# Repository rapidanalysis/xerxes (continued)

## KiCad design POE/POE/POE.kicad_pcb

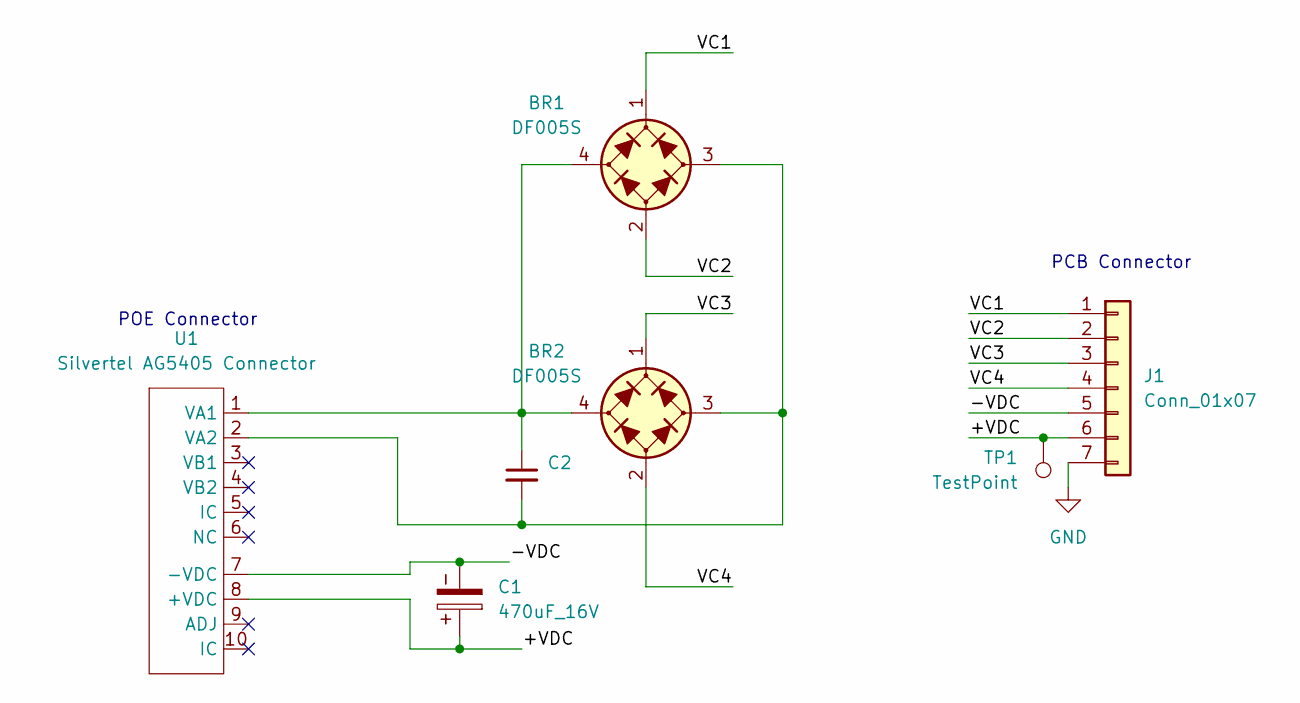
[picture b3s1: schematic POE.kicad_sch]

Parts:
BR1, BR2: DF005S; Diode_Bridge_Vishay_DFS
C1: 470uF_16V; CP_Radial_D8.0mm_P3.50mm
C2: 10nF; C_0402_1005Metric; Part Number 10 nf Capacitor 0402
J1: Conn_01x07; PinHeader_1x07_P2.54mm_Vertical
TP1: TestPoint; TestPoint_Pad_2.0x2.0mm
U1: Silvertel AG5405 Connector; AG5405

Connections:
/+VDC: C1.1, J1.6, TP1.1, U1.8 (+VDC)
/-VDC: C1.2, J1.5, U1.7 (-VDC)
/VC1: BR1.1 (+), J1.1
/VC2: BR1.2 (-), J1.2
/VC3: BR2.1 (+), J1.3
/VC4: BR2.2 (-), J1.4
GND: J1.7
unnamed: BR1.3 (1), BR2.3 (1), C2.2, U1.2 (VA2)
unnamed: BR1.4 (2), BR2.4 (2), C2.1, U1.1 (VA1)

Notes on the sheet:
POE Connector
PCB Connector

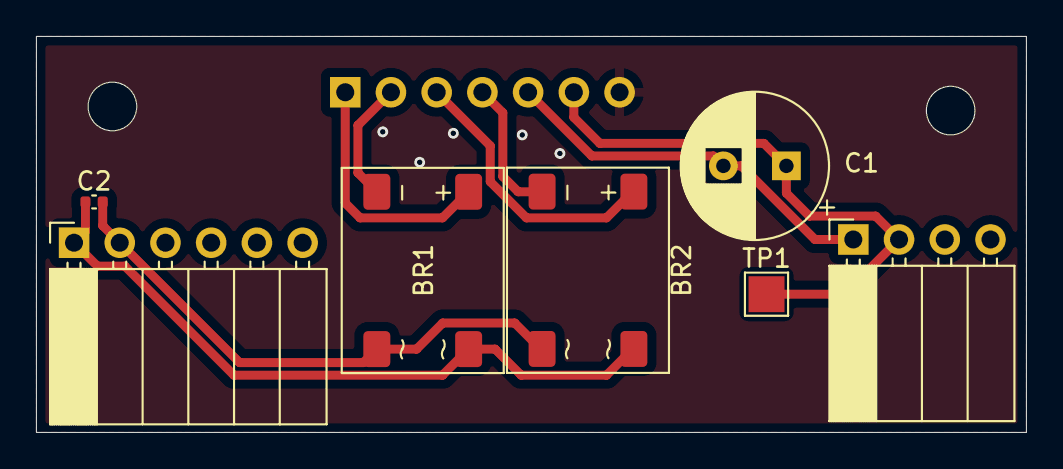
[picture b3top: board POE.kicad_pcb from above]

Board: 2 copper layers, 55.0 x 22.0 mm, 7 parts (1 on the bottom side), 8 nets.

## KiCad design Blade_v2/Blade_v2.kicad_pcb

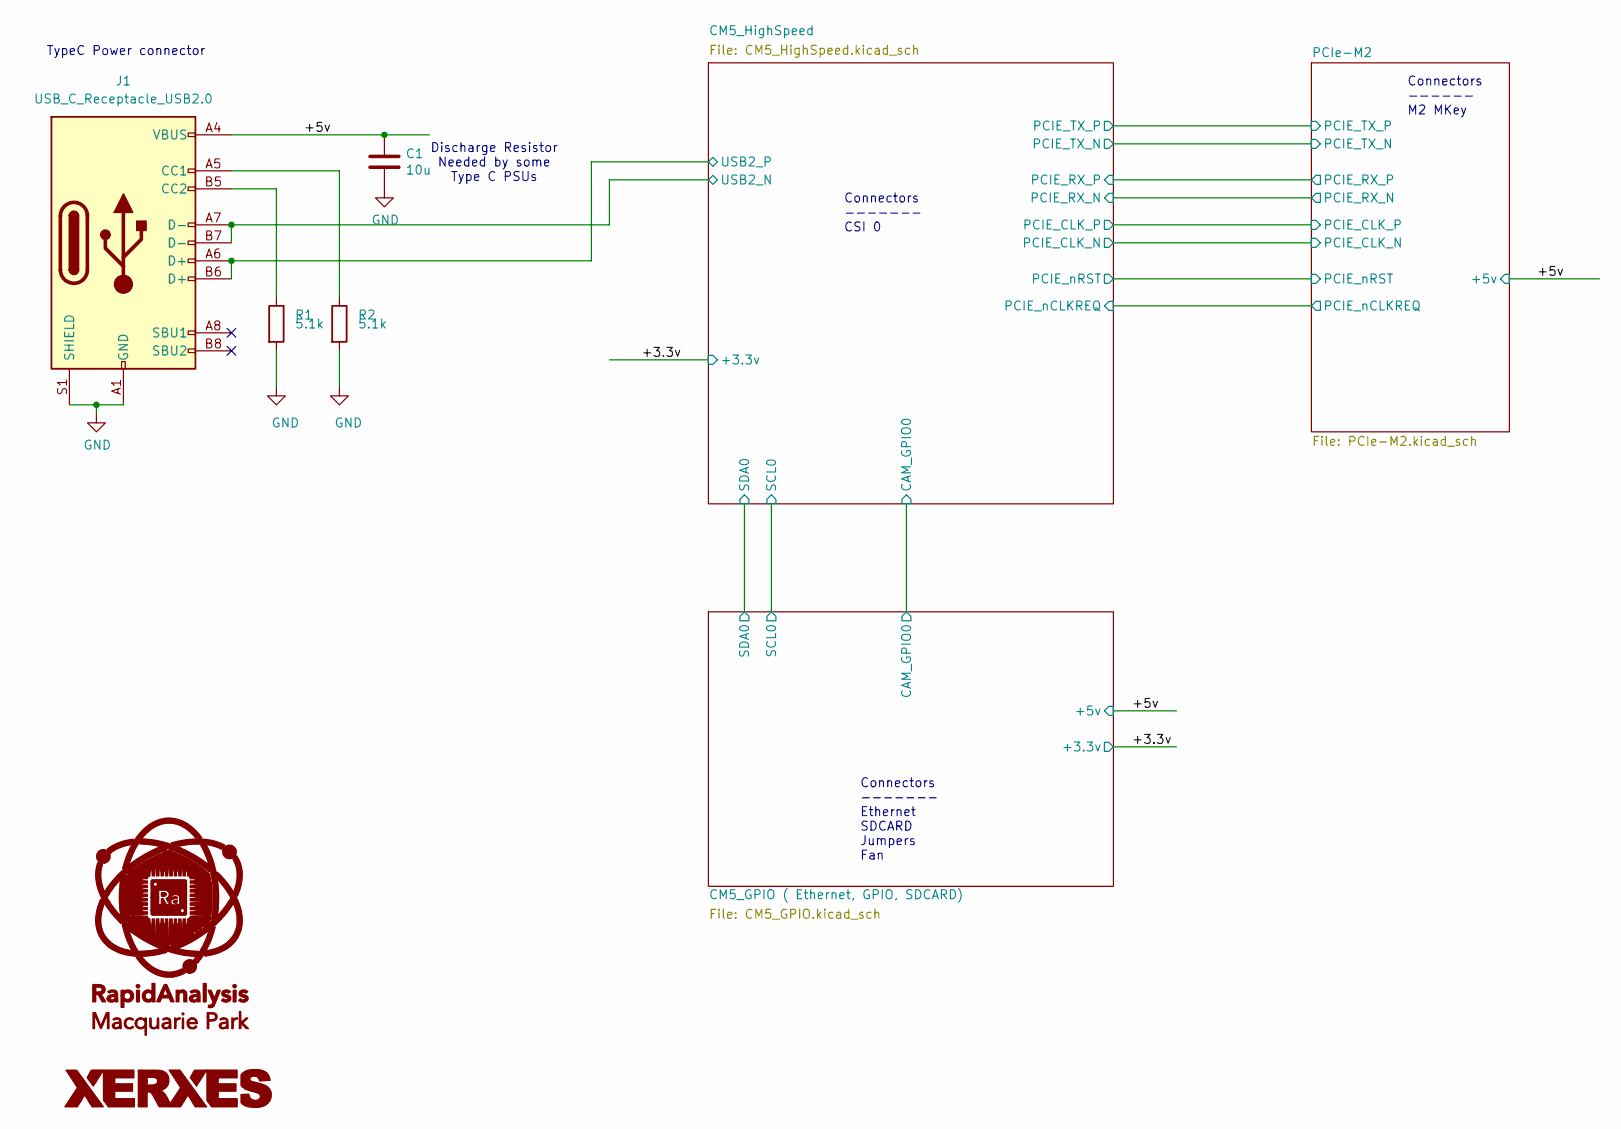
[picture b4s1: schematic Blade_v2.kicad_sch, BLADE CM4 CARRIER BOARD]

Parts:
C1: 10u; C_0402_1005Metric; Part Description 0.1uF 10% 16V Ceramic Capacitor X7R 040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
J1: USB_C_Receptacle_USB2.0; USB_C_Receptacle_GCT_USB4105-xx-A_16P_TopMnt_Horizontal; Part Description USBC USB2 data and power connector
R1, R2: 5.1k; R_0603_1608Metric_Pad0.98x0.95mm_HandSolder; MPN RC0603FR-075K1L; Digi-Key_PN 311-5.10KHRCT-ND

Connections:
/+5v: C1.1, J1.A4 (VBUS), J1.A9 (VBUS), J1.B4 (VBUS), J1.B9 (VBUS); also elsewhere on the board
/CM5_HighSpeed/USB2_N: J1.A7 (D-), J1.B7 (D-); also elsewhere on the board
/CM5_HighSpeed/USB2_P: J1.A6 (D+), J1.B6 (D+); also elsewhere on the board
GND: C1.2, J1.A1 (GND), J1.A12 (GND), J1.B1 (GND), J1.B12 (GND), J1.S1 (SHIELD), R1.2, R2.2; also elsewhere on the board
unnamed: J1.A5 (CC1), R2.1
unnamed: J1.B5 (CC2), R1.1

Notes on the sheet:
Connectors ------ M2 MKey
Connectors ------- Ethernet SDCARD Jumpers Fan
Discharge Resistor Needed by some Type C PSUs
Connectors ------- CSI 0
TypeC Power connector

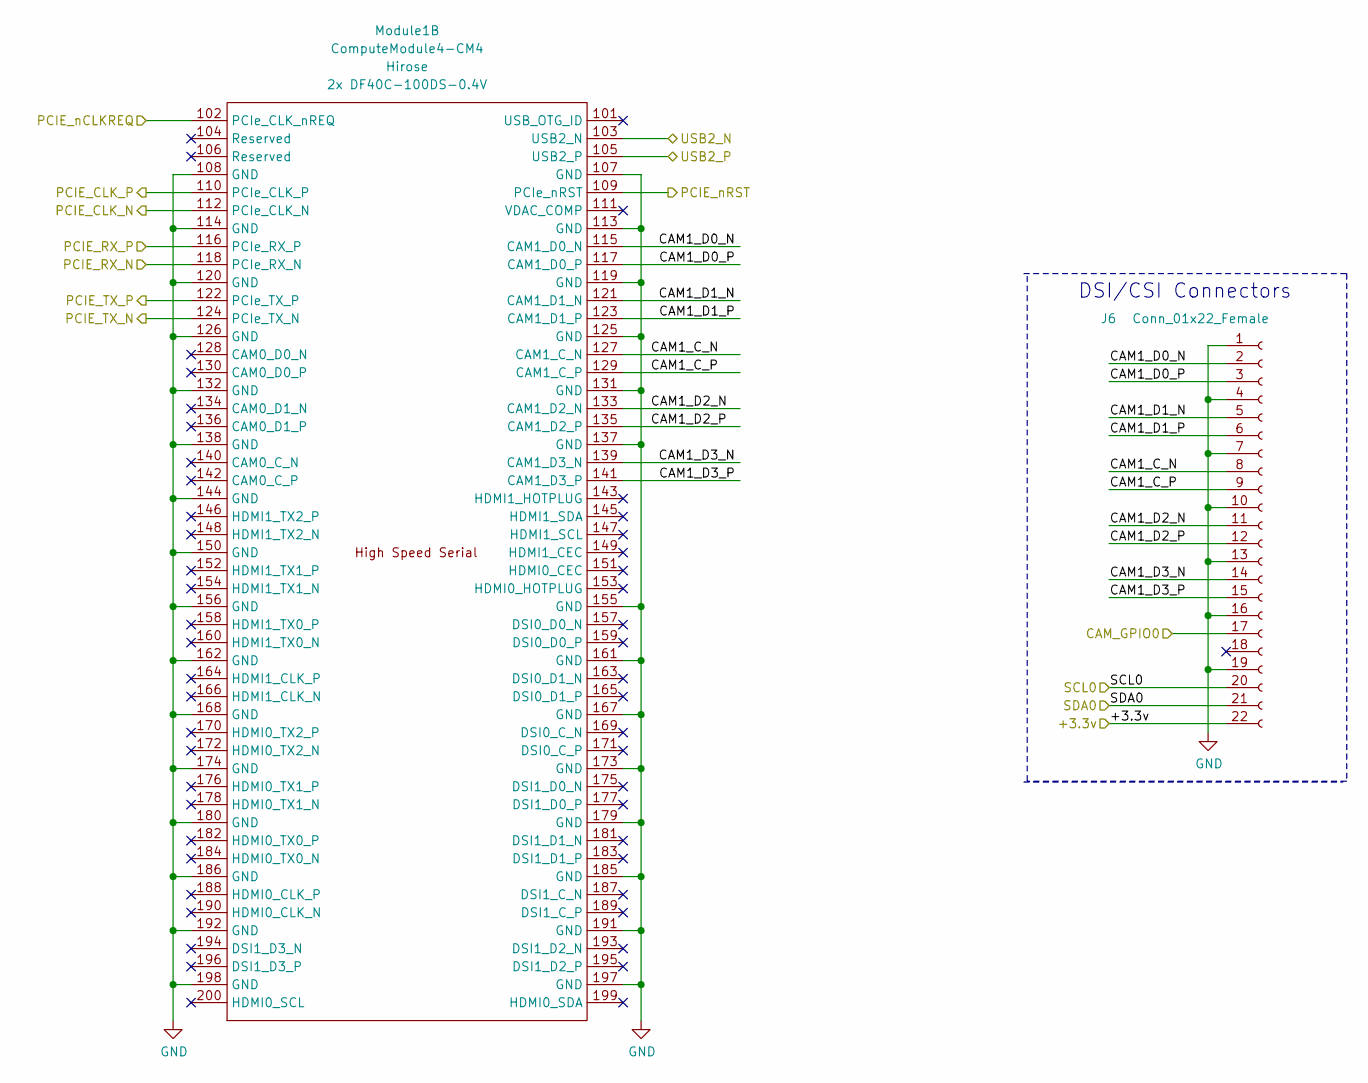
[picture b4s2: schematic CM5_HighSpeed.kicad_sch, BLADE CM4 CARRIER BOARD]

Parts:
J6: Conn_01x22_Female; Hirose_FH12-22S-0.5SH_1x22-1MP_P0.50mm_Horizontal; Part Description 22 Position FFC, FPC Connector Contacts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
Module1: ComputeModule4-CM4; Raspberry-Pi-4-Compute-Module

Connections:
/+3.3v: J6.22; also elsewhere on the board
/CM5_GPIO ( Ethernet, GPIO, SDCARD)/CAM_GPIO0: J6.17; also elsewhere on the board
/CM5_GPIO ( Ethernet, GPIO, SDCARD)/SCL0: J6.20; also elsewhere on the board
/CM5_GPIO ( Ethernet, GPIO, SDCARD)/SDA0: J6.21; also elsewhere on the board
/CM5_HighSpeed/CAM1_C_N: J6.8, Module1.127 (CAM1_C_N)
/CM5_HighSpeed/CAM1_C_P: J6.9, Module1.129 (CAM1_C_P)
/CM5_HighSpeed/CAM1_D0_N: J6.2, Module1.115 (CAM1_D0_N)
/CM5_HighSpeed/CAM1_D0_P: J6.3, Module1.117 (CAM1_D0_P)
/CM5_HighSpeed/CAM1_D1_N: J6.5, Module1.121 (CAM1_D1_N)
/CM5_HighSpeed/CAM1_D1_P: J6.6, Module1.123 (CAM1_D1_P)
/CM5_HighSpeed/CAM1_D2_N: J6.11, Module1.133 (CAM1_D2_N)
/CM5_HighSpeed/CAM1_D2_P: J6.12, Module1.135 (CAM1_D2_P)
/CM5_HighSpeed/CAM1_D3_N: J6.14, Module1.139 (CAM1_D3_N)
/CM5_HighSpeed/CAM1_D3_P: J6.15, Module1.141 (CAM1_D3_P)
/CM5_HighSpeed/PCIE_CLK_N: Module1.112 (PCIe_CLK_N); also elsewhere on the board
/CM5_HighSpeed/PCIE_CLK_P: Module1.110 (PCIe_CLK_P); also elsewhere on the board
/CM5_HighSpeed/PCIE_RX_N: Module1.118 (PCIe_RX_N); also elsewhere on the board
/CM5_HighSpeed/PCIE_RX_P: Module1.116 (PCIe_RX_P); also elsewhere on the board
/CM5_HighSpeed/PCIE_TX_N: Module1.124 (PCIe_TX_N); also elsewhere on the board
/CM5_HighSpeed/PCIE_TX_P: Module1.122 (PCIe_TX_P); also elsewhere on the board
/CM5_HighSpeed/PCIE_nCLKREQ: Module1.102 (PCIe_CLK_nREQ); also elsewhere on the board
/CM5_HighSpeed/PCIE_nRST: Module1.109 (PCIe_nRST); also elsewhere on the board
/CM5_HighSpeed/USB2_N: Module1.103 (USB2_N); also elsewhere on the board
/CM5_HighSpeed/USB2_P: Module1.105 (USB2_P); also elsewhere on the board
GND: J6.1, J6.4, J6.7, J6.10, J6.13, J6.16, J6.19, Module1.107 (GND), Module1.108 (GND), Module1.113 (GND), Module1.114 (GND), Module1.119 (GND), Module1.120 (GND), Module1.125 (GND), Module1.126 (GND), Module1.131 (GND), Module1.132 (GND), Module1.137 (GND), Module1.138 (GND), Module1.144 (GND), Module1.150 (GND), Module1.155 (GND), Module1.156 (GND), Module1.161 (GND), Module1.162 (GND), Module1.167 (GND), Module1.168 (GND), Module1.173 (GND), Module1.174 (GND), Module1.179 (GND), Module1.180 (GND), Module1.185 (GND), Module1.186 (GND), Module1.191 (GND), Module1.192 (GND), Module1.197 (GND), Module1.198 (GND); also elsewhere on the board

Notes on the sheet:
DSI/CSI Connectors

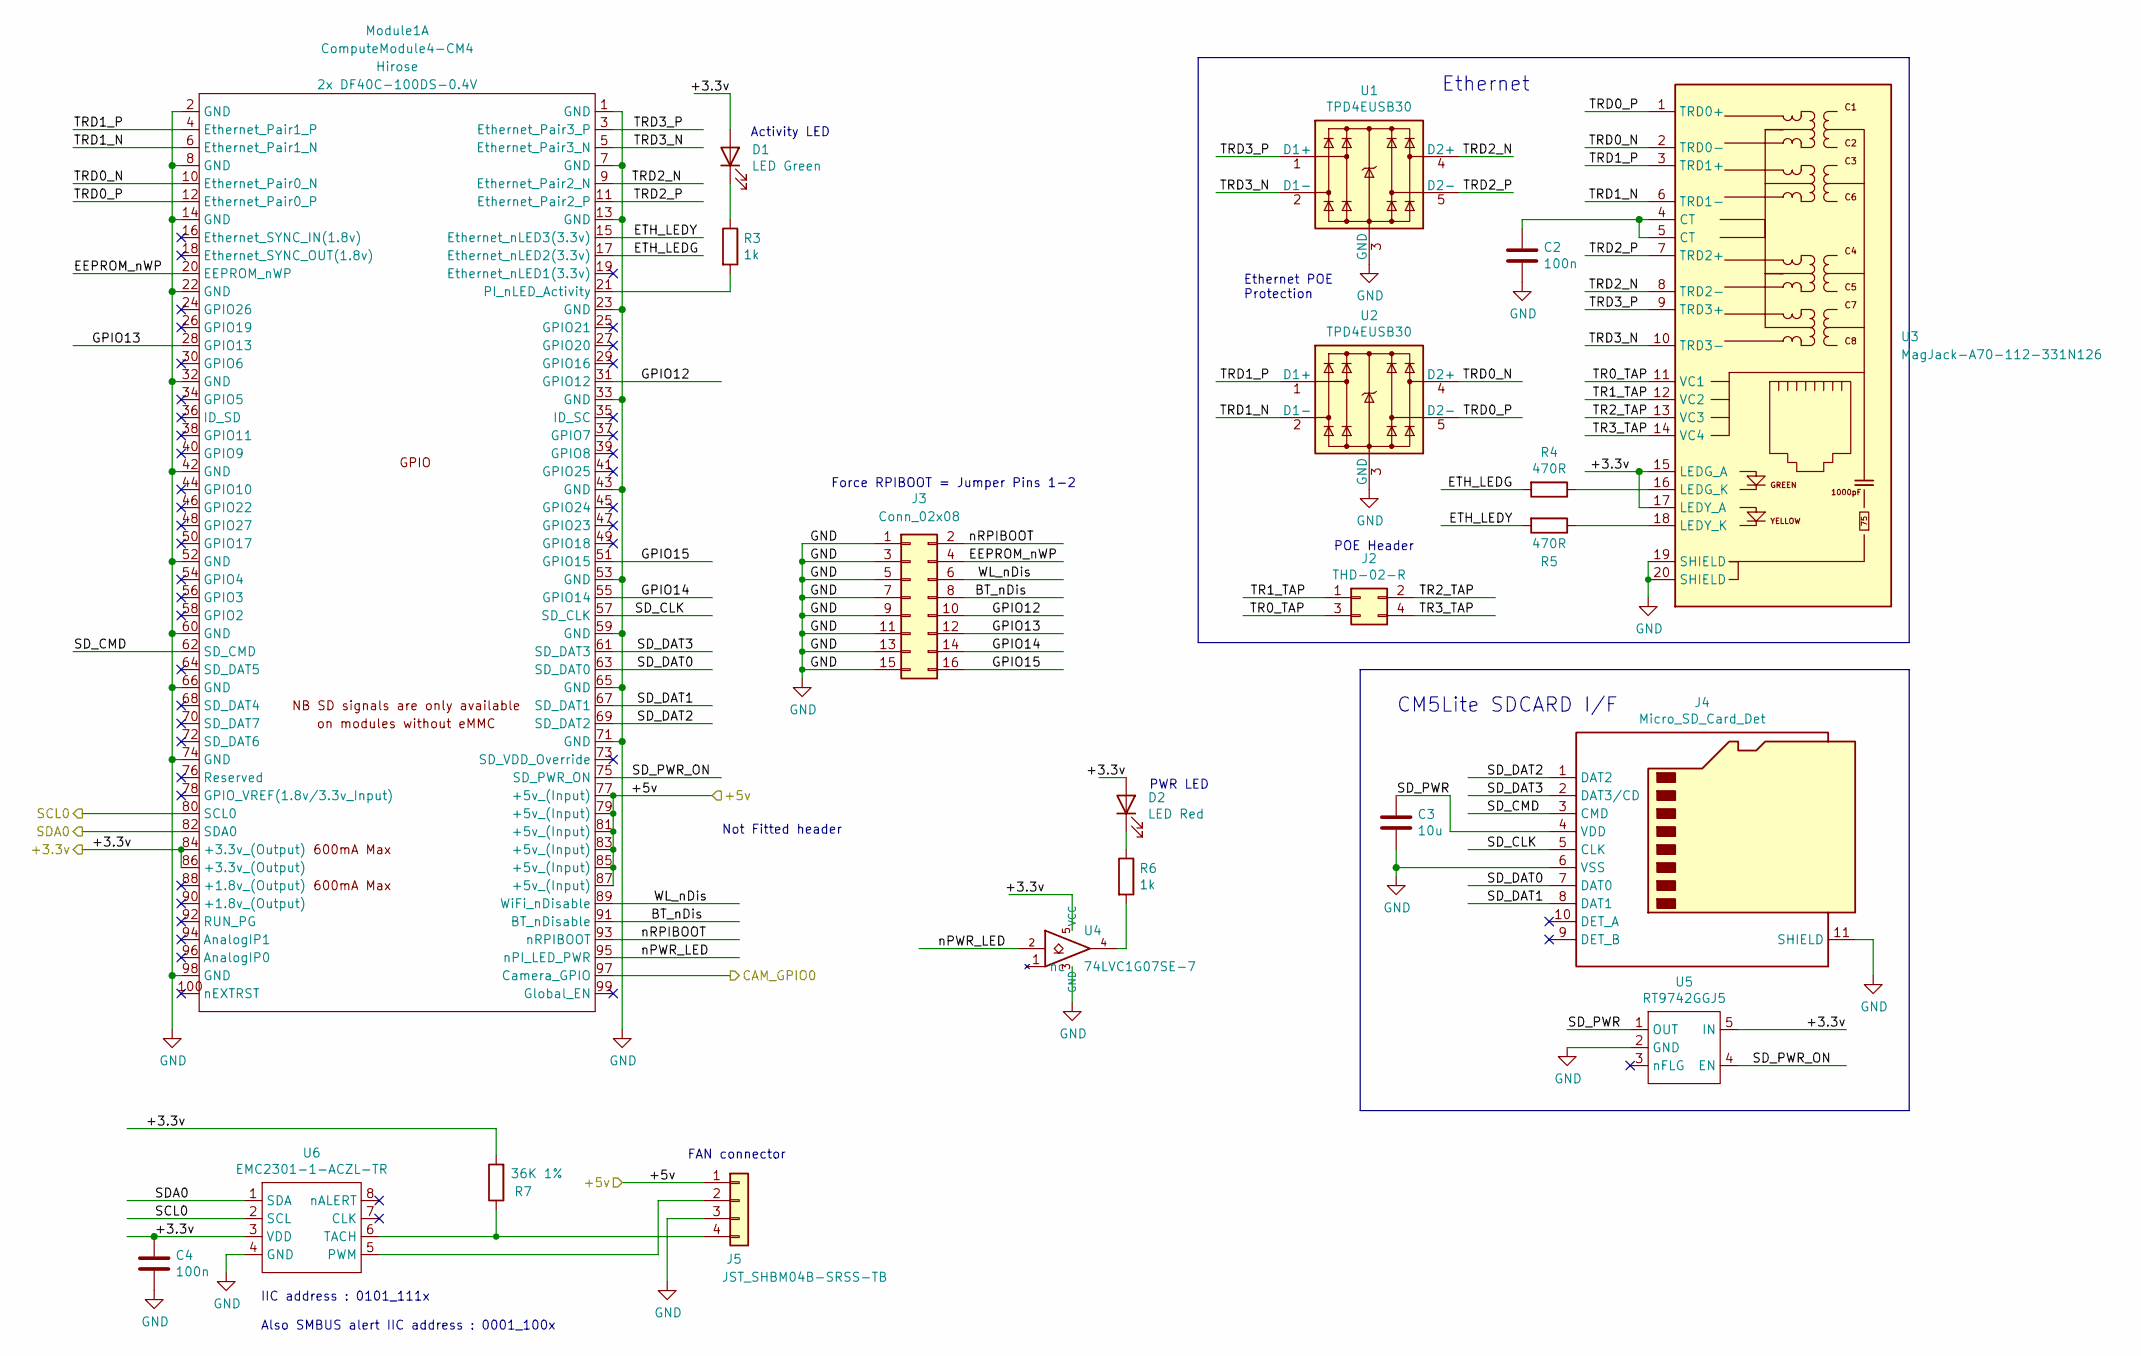
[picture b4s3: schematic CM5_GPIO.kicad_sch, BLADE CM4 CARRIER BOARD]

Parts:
C2, C4: 100n; C_0402_1005Metric; Part Description 0.1uF 10% 16V Ceramic Capacitor X7R 040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
C3: 10u; C_0805_2012Metric; Part Description 10uF 10% 10V Ceramic Capacitor X7R 0805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
D1: LED Green; LED_0603_1608Metric; Part Description Green 572nm LED Indication - Discrete 2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
D2: LED Red; LED_0603_1608Metric; Part Description Red 620nm LED Indication - Discrete 2.2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
J2: THD-02-R; PinHeader_2x02_P2.54mm_Vertical; Part Description PinHeader_2x02_P2.54mm_Vertical
J3: Conn_02x08; PinHeader_2x08_P2.54mm_Vertical; Part Number 1-1602FBV0T
J4: Micro_SD_Card_Det; SDCARD_MOLEX_503398-1892; Part Description 9 (8 + 1) Position Card Connector micro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
J5: JST_SHBM04B-SRSS-TB; JST_SH_BM04B-SRSS-TB_1x04-1MP_P1.00mm_Vertical; Part Description 4 pin vertical 1mm pitch connector
Module1: ComputeModule4-CM4; Raspberry-Pi-4-Compute-Module
R3, R6: 1k; R_0402_1005Metric; Part Description Resistor 1K M1005 1% 63mW
R4, R5: 470R; R_0402_1005Metric; Part Description Resistor 470R M1005 1% 63mW
R7: 36K 1%; R_0402_1005Metric; Part Description Resistor 36K M1005 1% 63mW
U1, U2: TPD4EUSB30; USON-10_2.5x1.0mm_P0.5mm; Part Description Quad TVS diode for high speed signals (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
U3: MagJack-A70-112-331N126; TRJG0926HENL
U4: 74LVC1G07SE-7; SOT-353_SC-70-5; Part Description Buffer, Non-Inverting 1 Element 1 Bit p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
U5: RT9742GGJ5; SOT-23-5; Part Description Power Switch/Driver 1:1 N-Channel 1A TS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
U6: EMC2301-1-ACZL-TR; MSOP-8_3x3mm_P0.65mm; Part Description Motor Driver PWM 8-MSOP

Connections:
/+3.3v: C4.1, D1.2 (A), D2.2 (A), Module1.84 (+3.3v_(Output)), Module1.86 (+3.3v_(Output)), R7.2, U3.15 (LEDG_A), U3.17 (LEDY_A), U4.5 (VCC), U5.5 (IN), U6.3 (VDD); also elsewhere on the board
/+5v: J5.1, Module1.77 (+5v_(Input)), Module1.79 (+5v_(Input)), Module1.81 (+5v_(Input)), Module1.83 (+5v_(Input)), Module1.85 (+5v_(Input)), Module1.87 (+5v_(Input)); also elsewhere on the board
/CM5_GPIO ( Ethernet, GPIO, SDCARD)/BT_nDis: J3.8 (+12V), Module1.91 (BT_nDisable)
/CM5_GPIO ( Ethernet, GPIO, SDCARD)/CAM_GPIO0: Module1.97 (Camera_GPIO); also elsewhere on the board
/CM5_GPIO ( Ethernet, GPIO, SDCARD)/EEPROM_nWP: J3.4, Module1.20 (EEPROM_nWP)
/CM5_GPIO ( Ethernet, GPIO, SDCARD)/ETH_LEDG: Module1.17 (Ethernet_nLED2(3.3v)), R4.2
/CM5_GPIO ( Ethernet, GPIO, SDCARD)/ETH_LEDY: Module1.15 (Ethernet_nLED3(3.3v)), R5.2
/CM5_GPIO ( Ethernet, GPIO, SDCARD)/GPIO12: J3.10 (GND), Module1.31 (GPIO12)
/CM5_GPIO ( Ethernet, GPIO, SDCARD)/GPIO13: J3.12 (GND), Module1.28 (GPIO13)
/CM5_GPIO ( Ethernet, GPIO, SDCARD)/GPIO14: J3.14 (-12V), Module1.55 (GPIO14)
/CM5_GPIO ( Ethernet, GPIO, SDCARD)/GPIO15: J3.16, Module1.51 (GPIO15)
/CM5_GPIO ( Ethernet, GPIO, SDCARD)/SCL0: Module1.80 (SCL0), U6.2 (SCL); also elsewhere on the board
/CM5_GPIO ( Ethernet, GPIO, SDCARD)/SDA0: Module1.82 (SDA0), U6.1 (SDA); also elsewhere on the board
/CM5_GPIO ( Ethernet, GPIO, SDCARD)/SD_CLK: J4.5 (CLK), Module1.57 (SD_CLK)
/CM5_GPIO ( Ethernet, GPIO, SDCARD)/SD_CMD: J4.3 (CMD), Module1.62 (SD_CMD)
/CM5_GPIO ( Ethernet, GPIO, SDCARD)/SD_DAT0: J4.7 (DAT0), Module1.63 (SD_DAT0)
/CM5_GPIO ( Ethernet, GPIO, SDCARD)/SD_DAT1: J4.8 (DAT1), Module1.67 (SD_DAT1)
/CM5_GPIO ( Ethernet, GPIO, SDCARD)/SD_DAT2: J4.1 (DAT2), Module1.69 (SD_DAT2)
/CM5_GPIO ( Ethernet, GPIO, SDCARD)/SD_DAT3: J4.2 (DAT3/CD), Module1.61 (SD_DAT3)
/CM5_GPIO ( Ethernet, GPIO, SDCARD)/SD_PWR: C3.1, J4.4 (VDD), U5.1 (OUT)
/CM5_GPIO ( Ethernet, GPIO, SDCARD)/SD_PWR_ON: Module1.75 (SD_PWR_ON), U5.4 (EN)
/CM5_GPIO ( Ethernet, GPIO, SDCARD)/TR0_TAP: J2.3, U3.11 (VC1)
/CM5_GPIO ( Ethernet, GPIO, SDCARD)/TR1_TAP: J2.1, U3.12 (VC2)
/CM5_GPIO ( Ethernet, GPIO, SDCARD)/TR2_TAP: J2.2, U3.13 (VC3)
/CM5_GPIO ( Ethernet, GPIO, SDCARD)/TR3_TAP: J2.4, U3.14 (VC4)
/CM5_GPIO ( Ethernet, GPIO, SDCARD)/TRD0_N: Module1.10 (Ethernet_Pair0_N), U2.4 (D2+), U2.7, U3.2 (TRD0-)
/CM5_GPIO ( Ethernet, GPIO, SDCARD)/TRD0_P: Module1.12 (Ethernet_Pair0_P), U2.5 (D2-), U2.6, U3.1 (TRD0+)
/CM5_GPIO ( Ethernet, GPIO, SDCARD)/TRD1_N: Module1.6 (Ethernet_Pair1_N), U2.2 (D1-), U2.9, U3.6 (TRD1-)
/CM5_GPIO ( Ethernet, GPIO, SDCARD)/TRD1_P: Module1.4 (Ethernet_Pair1_P), U2.1 (D1+), U2.10, U3.3 (TRD1+)
/CM5_GPIO ( Ethernet, GPIO, SDCARD)/TRD2_N: Module1.9 (Ethernet_Pair2_N), U1.4 (D2+), U1.7, U3.8 (TRD2-)
/CM5_GPIO ( Ethernet, GPIO, SDCARD)/TRD2_P: Module1.11 (Ethernet_Pair2_P), U1.5 (D2-), U1.6, U3.7 (TRD2+)
/CM5_GPIO ( Ethernet, GPIO, SDCARD)/TRD3_N: Module1.5 (Ethernet_Pair3_N), U1.2 (D1-), U1.9, U3.10 (TRD3-)
/CM5_GPIO ( Ethernet, GPIO, SDCARD)/TRD3_P: Module1.3 (Ethernet_Pair3_P), U1.1 (D1+), U1.10, U3.9 (TRD3+)
/CM5_GPIO ( Ethernet, GPIO, SDCARD)/WL_nDis: J3.6, Module1.89 (WiFi_nDisable)
/CM5_GPIO ( Ethernet, GPIO, SDCARD)/nPWR_LED: Module1.95 (nPI_LED_PWR), U4.2
/CM5_GPIO ( Ethernet, GPIO, SDCARD)/nRPIBOOT: J3.2, Module1.93 (nRPIBOOT)
GND: C2.2, C3.2, C4.2, J3.1, J3.3, J3.5 (+12V), J3.7 (12V), J3.9 (GND), J3.11 (GND), J3.13 (-12), J3.15 (-12V), J4.6 (VSS), J4.11 (SHIELD), J5.3, Module1.1 (GND), Module1.2 (GND), Module1.7 (GND), Module1.8 (GND), Module1.13 (GND), Module1.14 (GND), Module1.22 (GND), Module1.23 (GND), Module1.32 (GND), Module1.33 (GND), Module1.42 (GND), Module1.43 (GND), Module1.52 (GND), Module1.53 (GND), Module1.59 (GND), Module1.60 (GND), Module1.65 (GND), Module1.66 (GND), Module1.71 (GND), Module1.74 (GND), Module1.98 (GND), U1.3 (GND), U1.8 (GND), U2.3 (GND), U2.8 (GND), U3.19 (SHIELD), U3.20 (SHIELD), U4.3 (GND), U5.2 (GND), U6.4 (GND); also elsewhere on the board
unnamed: C2.1, U3.4 (CT), U3.5 (CT)
unnamed: D1.1 (K), R3.1
unnamed: D2.1 (K), R6.1
unnamed: J5.2, U6.5 (PWM)
unnamed: J5.4, R7.1, U6.6 (TACH)
unnamed: Module1.21 (PI_nLED_Activity), R3.2
unnamed: R6.2, U4.4
unnamed: R4.1, U3.16 (LEDG_K)
unnamed: R5.1, U3.18 (LEDY_K)

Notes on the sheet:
FAN connector
Activity LED
Ethernet POE Protection
IIC address : 0101_111x
Also SMBUS alert IIC address : 0001_100x
Not Fitted header
POE Header
Force RPIBOOT = Jumper Pins 1-2
PWR LED
Ethernet
CM5Lite SDCARD I/F

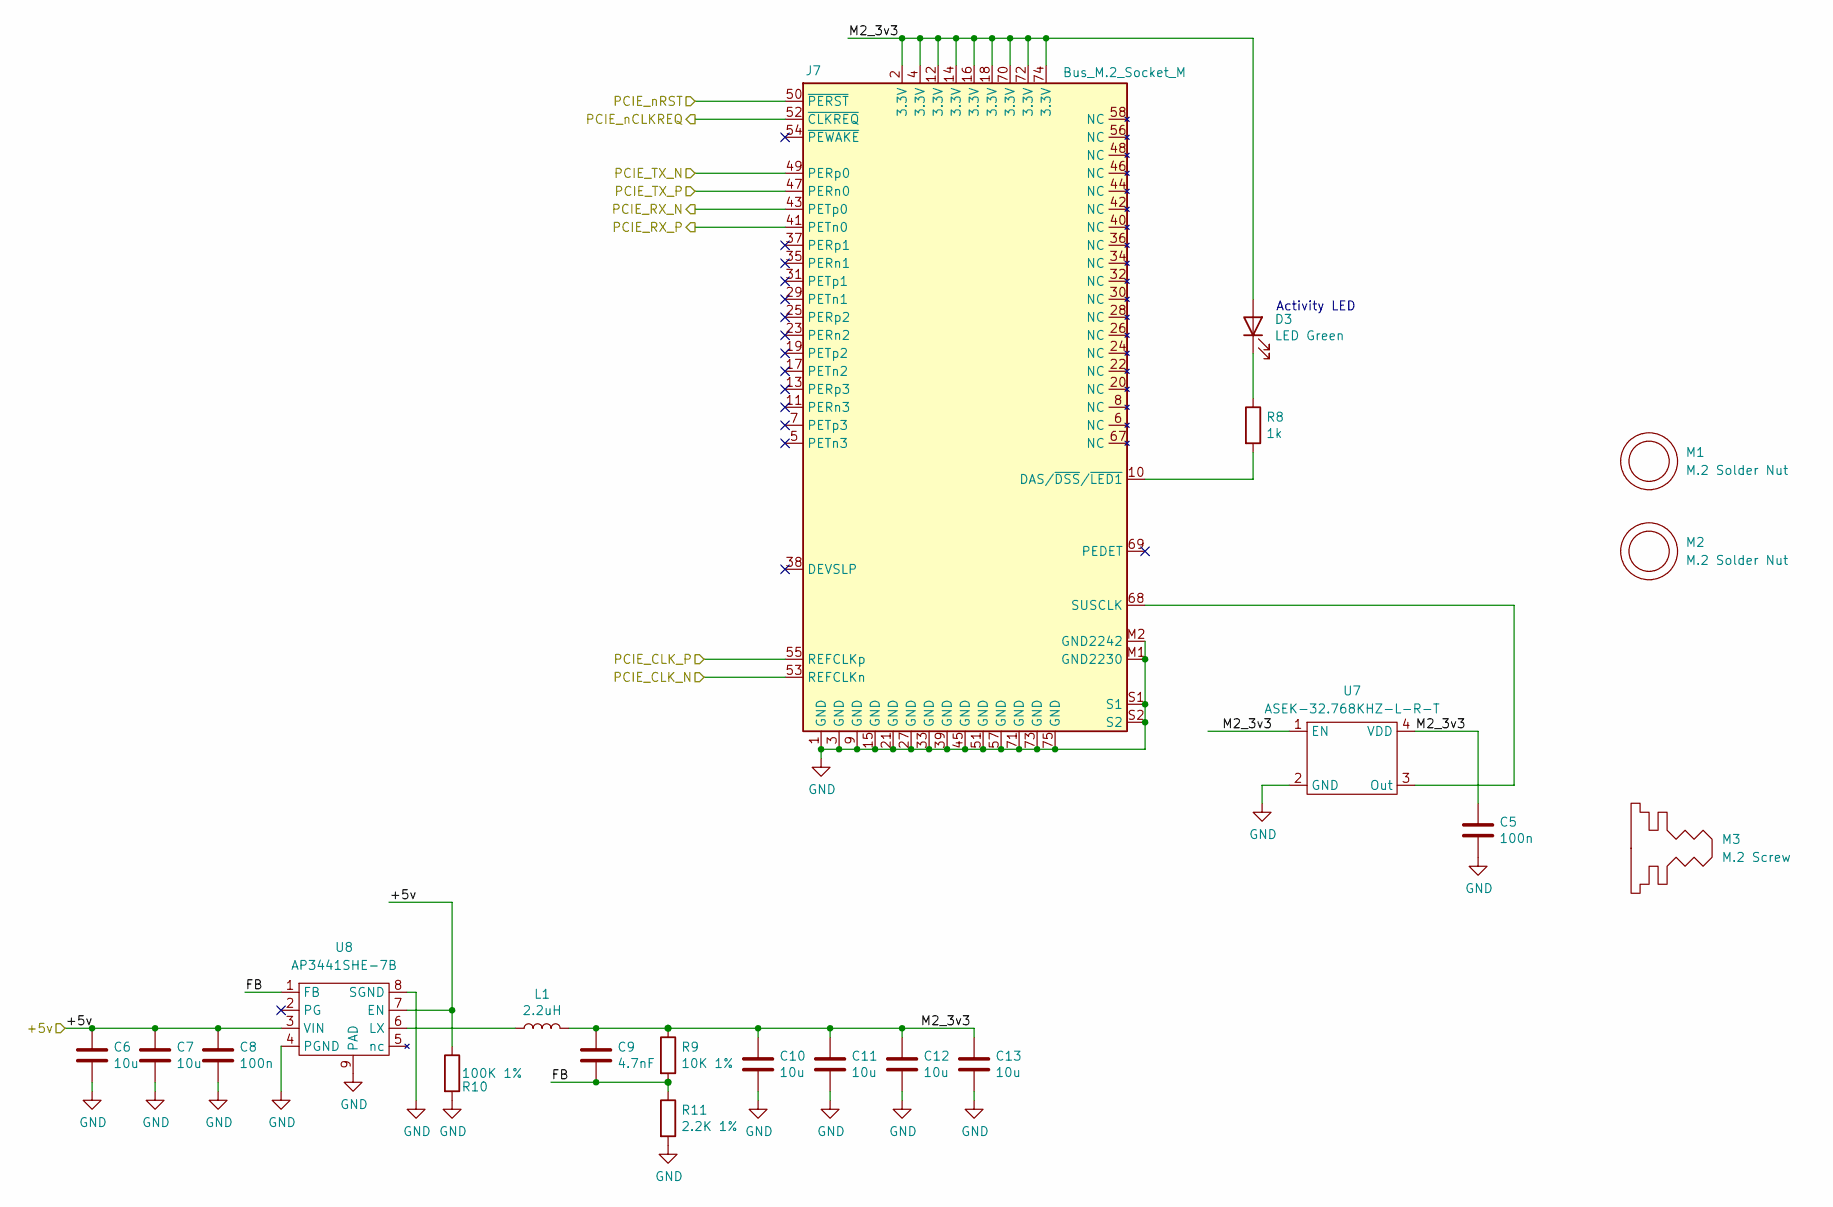
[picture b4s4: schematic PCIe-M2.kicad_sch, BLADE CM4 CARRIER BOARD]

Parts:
C5, C8: 100n; C_0402_1005Metric; Part Description 0.1uF 10% 16V Ceramic Capacitor X7R 040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
C6, C7, C10, C11, C12, C13: 10u; C_0805_2012Metric; Part Description 10uF 10% 10V Ceramic Capacitor X7R 0805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
C9: 4.7nF; C_0402_1005Metric; Part Description 4.7nF capacitor 0402
D3: LED Green; LED_0603_1608Metric; Part Description Green 572nm LED Indication - Discrete 2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
J7: Bus_M.2_Socket_M; M.2 M Key socket; Part Description M.2 M Key connector
L1: 2.2uH; L_Bourns_SRP5030CC; Part Description Inductor, SMT, 2520, 2u2, IRMS=7A, ISAT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
M1, M2: M.2 Solder Nut; Part Description Solder nut for M.2 slot
M3: M.2 Screw; Part Description M.2 Screw
R8: 1k; R_0402_1005Metric; Part Description Resistor 1K M1005 1% 63mW
R9: 10K 1%; R_0402_1005Metric; Part Description Resistor 10K M1005 1% 63mW
R10: 100K 1%; R_0402_1005Metric; Part Description Resistor 100K M1005 1% 63mW
R11: 2.2K 1%; R_0402_1005Metric; Part Description Resistor 2.2K M1005 1% 63mW
U7: ASEK-32.768KHZ-L-R-T; Crystal_SMD_3225-4Pin_3.2x2.5mm; Part Description 32KHz Xtal oscilator
U8: AP3441SHE-7B; DFN-8-1EP_2x2mm_P0.5mm_EP1.05x1.75mm; Part Description 3A DC-DC converter

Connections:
/+5v: C6.1, C7.1, C8.1, R10.1, U8.3 (VIN), U8.7 (EN); also elsewhere on the board
/CM5_HighSpeed/PCIE_CLK_N: J7.53 (REFCLKn); also elsewhere on the board
/CM5_HighSpeed/PCIE_CLK_P: J7.55 (REFCLKp); also elsewhere on the board
/CM5_HighSpeed/PCIE_RX_N: J7.43 (PETp0); also elsewhere on the board
/CM5_HighSpeed/PCIE_RX_P: J7.41 (PETn0); also elsewhere on the board
/CM5_HighSpeed/PCIE_TX_N: J7.49 (PERp0); also elsewhere on the board
/CM5_HighSpeed/PCIE_TX_P: J7.47 (PERn0); also elsewhere on the board
/CM5_HighSpeed/PCIE_nCLKREQ: J7.52 (~CLKREQ); also elsewhere on the board
/CM5_HighSpeed/PCIE_nRST: J7.50 (~PERST); also elsewhere on the board
/PCIe-M2/FB: C9.2, R9.2, R11.1, U8.1 (FB)
/PCIe-M2/M2_3v3: C5.1, C9.1, C10.1, C11.1, C12.1, C13.1, D3.2 (A), J7.2 (3.3V), J7.4 (3.3V), J7.12 (3.3V), J7.14 (3.3V), J7.16 (3.3V), J7.18 (3.3V), J7.70 (3.3V), J7.72 (3.3V), J7.74 (3.3V), L1.2, R9.1, U7.1 (EN), U7.4 (VDD)
GND: C5.2, C6.2, C7.2, C8.2, C10.2, C11.2, C12.2, C13.2, J7.1 (GND), J7.3 (GND), J7.9 (GND), J7.15 (GND), J7.21 (GND), J7.27 (GND), J7.33 (GND), J7.39 (GND), J7.45 (GND), J7.51 (GND), J7.57 (GND), J7.71 (GND), J7.73 (GND), J7.75 (GND), J7.M1 (GND2230), J7.M2 (GND2242), J7.S1, J7.S2, R10.2, R11.2, U7.2 (GND), U8.4 (PGND), U8.8 (SGND), U8.9 (PAD); also elsewhere on the board
unnamed: D3.1 (K), R8.1
unnamed: J7.10 (DAS/~DSS/~LED1), R8.2
unnamed: J7.68 (SUSCLK), U7.3 (Out)
unnamed: L1.1, U8.6 (LX)

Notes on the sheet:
Activity LED

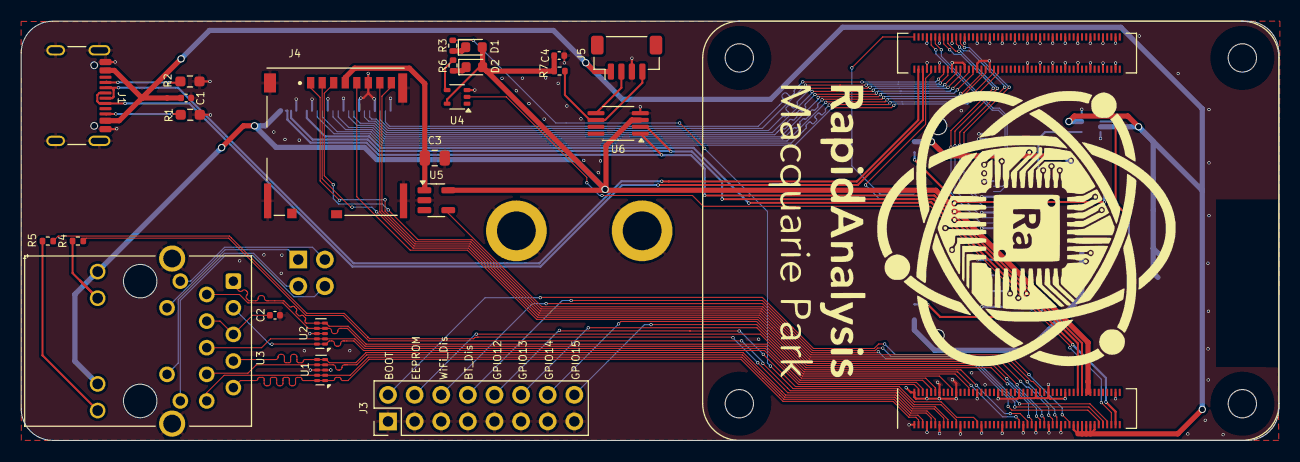
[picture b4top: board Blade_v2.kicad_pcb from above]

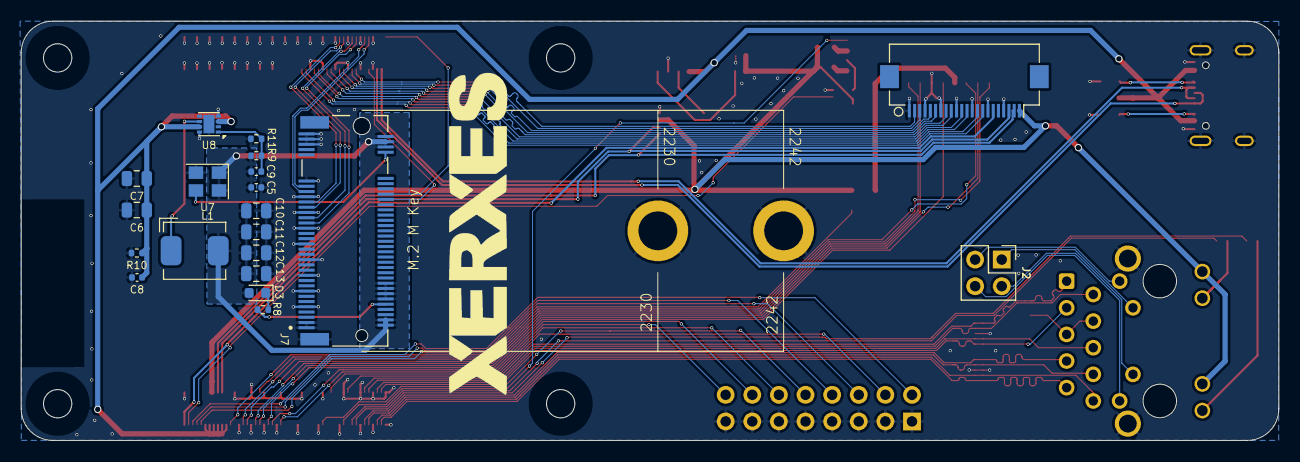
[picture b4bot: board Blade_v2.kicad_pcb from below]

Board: 2 copper layers, 120.0 x 40.0 mm, 44 parts (20 on the bottom side), 74 nets.
